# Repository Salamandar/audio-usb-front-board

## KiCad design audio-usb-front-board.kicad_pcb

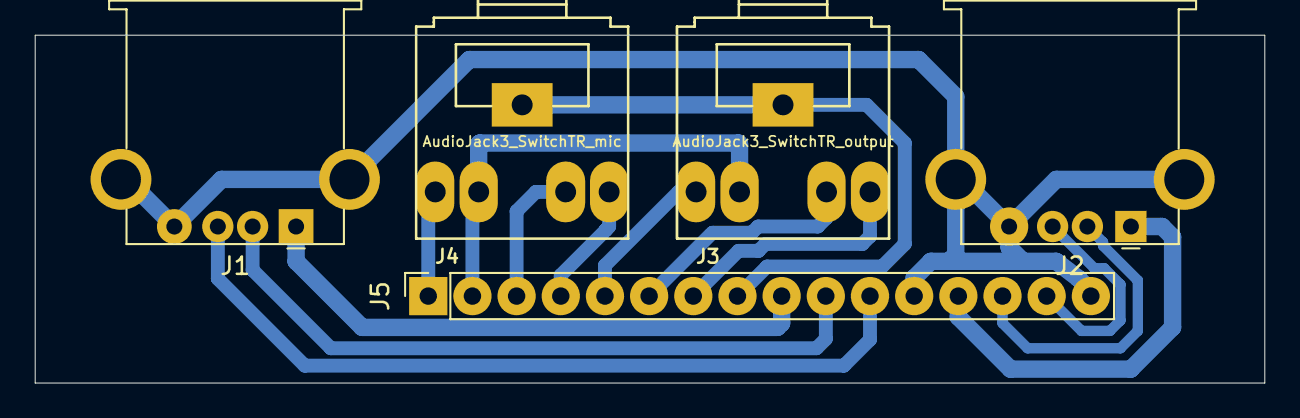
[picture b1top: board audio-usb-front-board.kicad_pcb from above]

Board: 2 copper layers, 70.7 x 20.0 mm, 5 parts (0 on the bottom side), 15 nets.

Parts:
J1: USB_A_right; USB_A_Stewart_SS-52100-001_Horizontal
J2: USB_A_left; USB_A_Stewart_SS-52100-001_Horizontal
J3: AudioJack3_SwitchTR_output; Tayda_3.5mm_stereo_TRS_jack_A-853
J4: AudioJack3_SwitchTR_mic; Tayda_3.5mm_stereo_TRS_jack_A-853
J5: Conn_01x16; PinSocket_1x16_P2.54mm_Vertical

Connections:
GND: J1.4, J1.5, J2.4, J2.5, J5.12, J5.16
unnamed: J1.1, J5.9
unnamed: J1.2, J5.10
unnamed: J1.3, J5.11
unnamed: J2.1, J5.13
unnamed: J2.2, J5.14
unnamed: J2.3, J5.15
unnamed: J3.R, J5.7
unnamed: J3.RN, J5.6
unnamed: J3.S, J4.S, J5.8
unnamed: J3.T, J5.5
unnamed: J3.TN, J4.TN, J5.2
unnamed: J4.R, J5.4
unnamed: J4.RN, J5.3
unnamed: J4.T, J5.1

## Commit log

2020-01-10 change sch a bit, change pad sizes
